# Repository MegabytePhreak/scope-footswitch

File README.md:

SCOPE-FOOTSWITCH
=================

STM32F401 based oscilloscope-footswitch interface using USBTMC.

Hardware is licensed CC-BY-SA-4.0
Software is GPLv3 for easy license compatibility with ChibiOS

Links:
* [Hackaday Coverage](https://hackaday.com/2018/12/02/keep-both-hands-on-the-probes-with-this-oscilloscope-footswitch/)
* [Initial Announcement](https://twitter.com/roukemap/status/1066811243237904384)
* [Rev.2 Batch](https://twitter.com/roukemap/status/1068734964215115776)
* [Custom Panels](https://twitter.com/roukemap/status/1072344658313908224)

Tools:

Other versions may work, this is just what is currently tested

HW:
* KiCAD 5.0.1

SW:
* arm-none-eabi-gcc (GNU Tools for ARM Embedded Processors 7-2018-q2-update) 7.3.1 20180622 (release) [ARM/embedded-7-branch revision 261907]
* GNU gdb (GNU Tools for ARM Embedded Processors 7-2018-q2-update) 8.1.0.20180315-git
* ChibiOS-RT with community USB Host framework
* libopencm3 and DFU code from BlackMagicProbe

This repo uses several submodules, make sure they are up to date.
After checking out the kicad-library repo, make sure to cd to it and run make to generate the actual KiCAD libraries.

SW Build Process:
1. Make sure the arm-none-eabi toolchain is on your path: `which arm-none-eabi-gcc`
2. Pre-build the libopencm3 library: `cd sw/ext/libopencm3 && make -j && cd ../../..`
3. Build the bootloader: `cd sw/bootloader && make -j && cd ../..`
4. Build the main application: `cd sw/scope-footswitch && make -j && cd ../..`

SW Programming process:
1. Connect SWD debugger (e.g. blackmagicprobe) to hardware
2. Connect micro-usb from pc to hardware
3. `cd sw/bootloader`
4. `./flash.sh`
5. Power cycle hardware, holding down the front panel button to force entry to the bootloader
6. `cd ../scope-footswitch`
7. `./dfu.sh`

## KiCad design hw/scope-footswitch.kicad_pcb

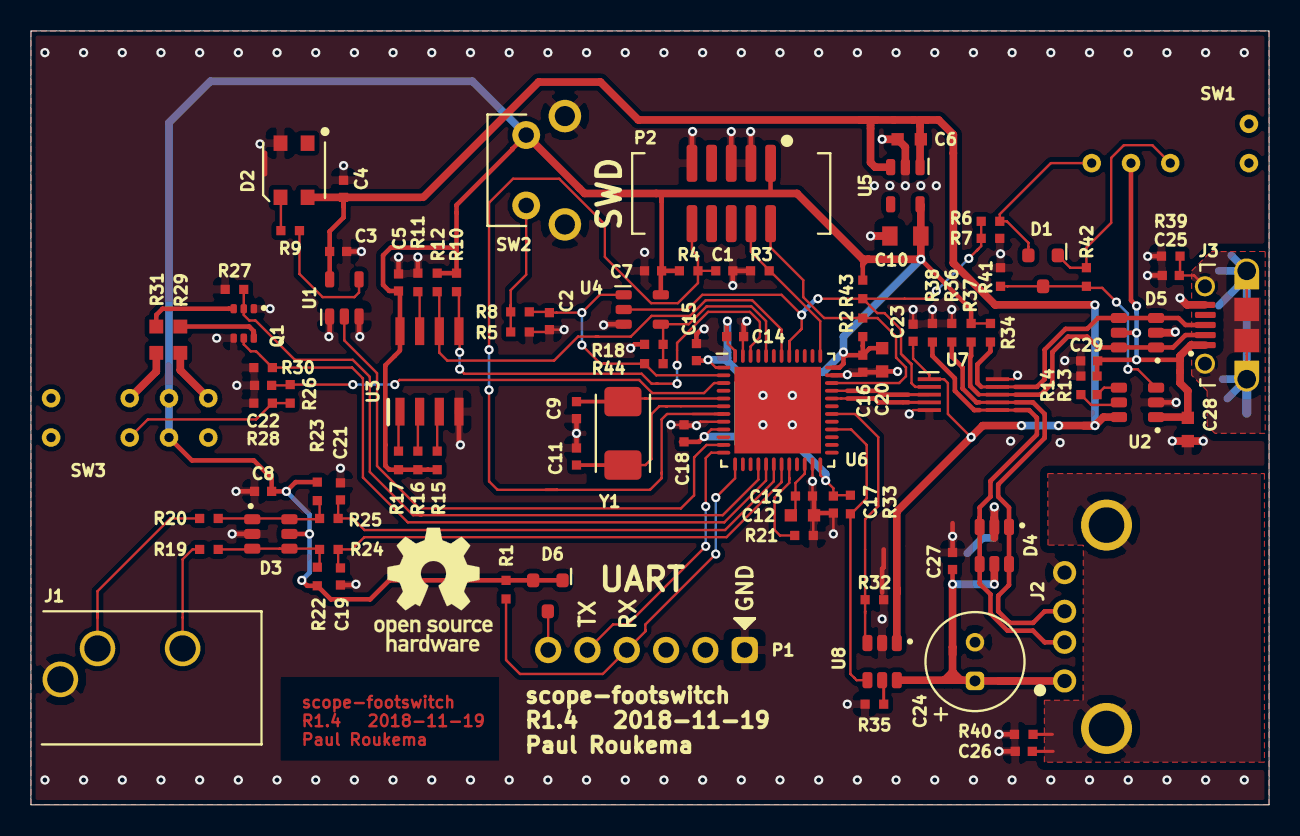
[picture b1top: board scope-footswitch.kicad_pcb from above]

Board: 2 copper layers, 80.0 x 50.0 mm, 98 parts (0 on the bottom side), 58 nets.

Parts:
C1, C2, C3, C4, C5, C7, C8, C13, C14, C15, C16, C17, C18, C19, C21, C22, C23, C27, C29: C00001; C_0402_1005M
C6, C20, C28: C00002; C_0603_1608M
C9, C11: C00033; C_0402_1005M
C10: C00004; C_0805_2012M
C12: C00007; C_0603_1608M
C24: C00003; CRADIAL_6.3x11.2_2.5
C25, C26: C00027; C_0402_1005M
D1, D6: D00006; SOT_3_950_2900X1300X1000_ONSEMI
D2: LED00006; LED_3535_NEOPIXEL_MINI
D3, D4, D5: D00003; SOT_6_950_2900X1600X1100
J1: CN00050; J_CUI_SJ1-3533NG
J2: CN00049; J_AMPHENOL_UE27AC54100
J3: CN00023; J_FCI_10118194
M1: M00028; OSHW-Logo_7.5x8mm_SilkScreen
P1: CN00052; P_FCI_68000-206
P2: CN00051; P_CNC_3221-10-0300-00
Q1: Q00002; SOT_6_650_2150X1300x1100_DIODES
R1, R4, R5, R6, R8, R11, R13, R15, R16, R17, R18, R21, R22, R23, R24, R25, R26, R27, R28, R30, R32, R33, R41: R00014; R_0402_1005M
R2, R3, R35: R00016; R_0402_1005M
R7, R36, R38: R00056; R_0402_1005M
R9: R00037; R_0402_1005M
R10, R12: R00038; R_0402_1005M
R14: R00009; R_0402_1005M
R19, R20: R00011; R_0402_1005M
R29, R31: R00080; R_0603_1608M
R34, R37: R00081; R_0402_1005M
R39, R40: R00008; R_0402_1005M
R42, R44: R00001; R_0402_1005M
R43: R00046; R_0402_1005M
SW1: M00027; SW_NKK_G13AV
SW2: M00012; SW_TL1105JA
SW3: M00026; SW_NKK_G12JVCF
U1: U00054; SOT_5_950_2900X1600X1100_DIODES
U2, U8: U00086; SOT_6_950_2800x1600x110_DIODES_SOT26
U3: U00055; SOIC_8_1270_4900X3900X1750
U4: U00087; SOT_5_950_2900X1600X1100_DIODES
U5: U00049; SOT_5_950_2900X1600X1100_DIODES
U6: U00084; QFN_48_500_7000X7000X600_ST
U7: U00085; MSOP_10_500_3000X3000X1100_ONSEMI
Y1: Y00015; XTAL_2_5000X3200X1300_ABRACON

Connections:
+3V3: C5.1, C7.1, C8.1, C10.1, C14.1, C15.1, C16.1, C17.1, C18.1, C20.2, D3.5, D6.1, D6.2, P2.1, R1.1, R2.1, R4.1, R10.2, R12.1, R15.2, R16.2, R17.2, R22.1, R23.1, R33.1, R34.1, R37.1, R43.2, SW2.1, SW3.2, SW3.5, U3.8, U4.5, U5.5, U6.1, U6.9, U6.24, U6.36, U6.48
+5V: C3.1, C4.1, C6.2, C23.1, D2.4, U1.5, U2.6, U5.1, U5.3, U7.1, U8.1
/BOOT0: R18.1, R44.1, U4.4, U6.44
/BOOT1: R21.2, U6.20
/BTN: C2.1, R8.2, R44.2, U4.1, U6.2
/BTN_R: R5.1, R8.1, SW2.2
/DEVICE_DM: D5.1, D5.6, J3.2, R37.2, U7.8
/DEVICE_DP: D5.3, D5.4, J3.3, R34.2, U7.9
/DEVICE_SHIELD: C25.1, J3.M1, J3.M2, J3.M3, J3.M4, J3.M5, J3.M6, R39.2
/EN_DEVICE: R6.1, R7.2, R43.1, U4.2, U6.41, U7.2
/EN_DEVICE_5V: D1.2, R6.2, SW1.4
/EN_HOST_5V: D1.1, R42.1, SW1.6
/FOOTSW_BTN1: C21.1, R25.2, U6.18
/FOOTSW_BTN1_R: D3.1, D3.6, R20.1, R23.2, R25.1
/FOOTSW_BTN2: C19.1, R24.2, U6.19
/FOOTSW_BTN2_R: D3.3, D3.4, R19.1, R22.2, R24.1
/HOST_DM: D4.3, D4.4, J2.2, R38.1, U7.6
/HOST_DP: D4.1, D4.6, J2.3, R36.1, U7.7
/HOST_FAULT_N: R33.2, U6.28, U8.4
/HOST_ILIM: R35.1, U8.5
/HOST_SHIELD: C26.1, J2.M1, J2.M2, R40.2
/HOST_VBUS: C24.+, C27.1, D4.5, J2.1, U8.6
/HOST_VBUS_EN: R32.1, U6.30, U8.3
/I2C_SCL: R12.2, U3.6, U6.42
/I2C_SDA: R10.1, U3.5, U6.46
/LED_DATA: D2.3, R9.1
/LED_DATA_LS: U1.2, U6.11
/LED_DATA_R: R9.2, U1.4
/MODE: C22.1, R26.2, U6.3
/MODE_LED_G: Q1.5, R30.1, U6.17
/MODE_LED_R: Q1.2, R27.1, U6.16
/MODE_R: R26.1, R28.1, SW3.3
/NRST: C1.1, P2.10, R4.2, U6.7
/PWR_EN: D1.3, R41.2, R42.2, U2.3
/STM32_DM: U6.32, U7.4
/STM32_DP: U6.33, U7.3
/SWDCLK: P2.4, R3.1, U6.37
/SWDIO: P2.2, R2.2, U6.34
/UART_RX: P1.4, R1.2, U6.13
/UART_TX: P1.5, U6.12
/VCAP: C12.2, C13.1, U6.22
/VIN_FAULT_N: R13.2, U2.4
/VIN_ILIM: R14.1, U2.5
GND: C1.2, C2.2, C3.2, C4.2, C5.2, C6.1, C7.2, C8.2, C9.1, C10.2, C11.1, C12.1, C13.2, C14.2, C15.2, C16.2, C17.2, C18.2, C19.2, C20.1, C21.2, C22.2, C23.2, C24.-, C25.2, C26.2, C27.2, C28.1, C29.2, D2.2, D3.2, D4.2, D5.2, J1.1, J2.4, J3.5, P1.1, P2.3, P2.5, P2.9, Q1.1, Q1.4, R3.2, R5.2, R7.1, R11.1, R14.2, R18.2, R21.1, R27.2, R28.2, R30.2, R32.2, R35.2, R36.2, R38.2, R39.1, R40.1, R41.1, SW2.M1, SW2.M2, U1.1, U1.3, U2.2, U3.4, U4.3, U5.2, U6.8, U6.23, U6.35, U6.47, U6.49, U7.5, U7.10, U8.2
unnamed: C9.2, U6.5, Y1.1
unnamed: C11.2, U6.6, Y1.2
unnamed: D6.3, P1.6
unnamed: J1.2, R20.2
unnamed: J1.3, R19.2
unnamed: Q1.3, R31.2
unnamed: Q1.6, R29.2
unnamed: R11.2, U3.7
unnamed: R15.1, U3.3
unnamed: R16.1, U3.2
unnamed: R17.1, U3.1
unnamed: R29.1, SW3.4
unnamed: R31.1, SW3.6
VBUS: C28.2, C29.1, D5.5, J3.1, R13.1, SW1.5, U2.1

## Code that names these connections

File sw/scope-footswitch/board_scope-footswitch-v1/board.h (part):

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 *
 * PA0  - UNUSED                    (input pullup).
 * PA1  - GPIOA_LED_DATA_LS         (alternate 2 - TIM5_CH2).
 * PA2  - UART_TX                   (alternate 7 - USART2_TX).
 * PA3  - UART_RX                   (alternate 7 - USART2_RX).
 * PA4  - UNUSED                    (input pullup).
 * PA5  - UNUSED                    (input pullup).
 * PA6  - MODE_LED_R                (alternate 3 - TIM3_CH1).
 * PA7  - MODE_LED_G                (alternate 3 - TIM3_CH2).
 * PA8  - UNUSED                    (input pullup).
 * PA9  - HOST_VBUS_EN              (output pushpull).
 * PA10 - UNUSED                    (input pullup).
 * PA11 - STM32_DM                  (alternate 10 - OTG_FS_DM).
 * PA12 - STM32_DP                  (alternate 10 - OTG_FS_DP).
 * PA13 - SWDIO                     (alternate 0 - SWDIO).
 * PA14 - SWCLK                     (alternate 0 - SWCLK).
 * PA15 - UNUSED                    (input pullup).
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/*
 * GPIOB setup:
 *
 * PB0  - FOOTSW_BTN1               (input pullup).
 * PB1  - FOOTSW_BTN2               (input pullup).
 * PB2  - BOOT1                     (input pullup).
 * PB3  - UNUSED                    (input pullup).
 * PB4  - UNUSED                    (input pullup).
 * PB5  - EN_DEVICE                 (input pullup).
 * PB6  - I2C_SCL                   (alternate 4 - I2C1_SCL).
 * PB7  - UNUSED                    (input pullup).
 * PB8  - UNUSED                    (input pullup).
 * PB9  - I2C_SDA                   (alternate 4 - I2C1_SDA).
 * PB10 - UNUSED                    (input pullup).
 * PB11 - UNUSED                    (input pullup).
 * PB12 - UNUSED                    (input pullup).
 * PB13 - UNUSED                    (input pullup).
 * PB14 - UNUSED                    (input pullup).
 * PB15 - HOST_FAULT_N              (input pullup).
 */
#define VAL_GPIOB_MODER             (PIN_MODE_INPUT(GPIOB_FOOTSW_BTN1) |    \
                                     PIN_MODE_INPUT(GPIOB_FOOTSW_BTN2) |    \
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 * PC10 - NC                        (input pullup).
 * PC11 - NC                        (input pullup).
 * PC12 - NC                        (input pullup).
 * PC13 - BTN                       (input pullup).
 * PC14 - MODE                      (input pullup).
 * PC15 - UNUSED                    (input pullup).
 */
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
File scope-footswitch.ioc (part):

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Mcu.Name=STM32F401C(B-C)Ux
Mcu.Package=UFQFPN48
Mcu.UserName=STM32F401CBUx
PA1.GPIOParameters=GPIO_Label
PA1.GPIO_Label=LED_DATA_LS
PA1.Signal=S_TIM5_CH2
PA11.GPIOParameters=GPIO_Label
PA11.GPIO_Label=STM32_DM
PA11.Mode=Device_Only
PA11.Signal=USB_OTG_FS_DM
PA12.GPIOParameters=GPIO_Label
PA12.GPIO_Label=STM32_DP
PA12.Mode=Device_Only
PA12.Signal=USB_OTG_FS_DP
PA13.GPIOParameters=GPIO_Label
PA13.GPIO_Label=SWDIO
PA13.Mode=Serial_Wire
PA13.Signal=SYS_JTMS-SWDIO
PA14.GPIOParameters=GPIO_Label
PA14.GPIO_Label=SWDCLK
PA14.Mode=Serial_Wire
PA14.Signal=SYS_JTCK-SWCLK
PA15.Signal=SYS_JTDI
PA2.GPIOParameters=GPIO_Label
PA2.GPIO_Label=UART_TX
PA2.Mode=Asynchronous
PA2.Signal=USART2_TX
PA3.GPIOParameters=GPIO_Label
PA3.GPIO_Label=UART_RX
PA3.Mode=Asynchronous
PA3.Signal=USART2_RX
PA6.GPIOParameters=GPIO_Label
PA6.GPIO_Label=MODE_LED_R
PA6.Signal=S_TIM3_CH1
PA7.GPIOParameters=GPIO_Label
PA7.GPIO_Label=MODE_LED_G
PA7.Signal=S_TIM3_CH2
PA9.GPIOParameters=GPIO_Label
PA9.GPIO_Label=HOST_VBUS_EN
PA9.Signal=GPIO_Output
PB0.GPIOParameters=GPIO_Label
PB0.GPIO_Label=FOOTSWITCH_BTN1
PB0.Signal=GPXTI0
PB1.GPIOParameters=GPIO_Label
PB1.GPIO_Label=FOOTSWITCH_BTN2
PB1.Signal=GPXTI1
PB15.GPIOParameters=GPIO_Label
PB15.GPIO_Label=HOST_FAULT_N
PB15.Signal=GPXTI15
PB2.GPIOParameters=GPIO_Label
PB2.GPIO_Label=BOOT1
PB2.Signal=GPIO_Input
PB4.Signal=SYS_JTRST
PB5.GPIOParameters=GPIO_Label
PB5.GPIO_Label=EN_DEVICE
PB5.Signal=GPXTI5
PB6.GPIOParameters=GPIO_Label
PB6.GPIO_Label=ISC_SCL
PB6.Mode=I2C
PB6.Signal=I2C1_SCL
PB9.GPIOParameters=GPIO_Label
PB9.GPIO_Label=I2C_SDA
PB9.Mode=I2C
PB9.Signal=I2C1_SDA
PC13-ANTI_TAMP.GPIOParameters=GPIO_Label
PC13-ANTI_TAMP.GPIO_Label=BTN
PC13-ANTI_TAMP.Signal=GPXTI13
PC14-OSC32_IN.GPIOParameters=GPIO_Label
PC14-OSC32_IN.GPIO_Label=MODE
PC14-OSC32_IN.Signal=GPXTI14
PH0\ -\ OSC_IN.Mode=HSE-External-Oscillator
PH0\ -\ OSC_IN.Signal=RCC_OSC_IN
PH1\ -\ OSC_OUT.Mode=HSE-External-Oscillator
PH1\ -\ OSC_OUT.Signal=RCC_OSC_OUT
RCC.HSE_VALUE=8000000
RCC.SYSCLKFreq_VALUE=72000000
RCC.SYSCLKSource=RCC_SYSCLKSOURCE_PLLCLK
board=custom

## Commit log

2018-08-06 Initial add of HW
2018-08-06 Add ChibiOS modules
2018-08-06 Add project for USB host on Nucleo board
2018-08-06 Add kicad library tables
2018-08-06 Add component documentation
2018-08-11 Initial completion of schematic and layout
2018-08-13 PCB updates and output files
2018-08-16 Layout V1.1 Fix unconnected vias, pour under crystal, USB switch pads
2018-08-25 Sync to Chibios Stable
2018-08-25 Initial TMC emulator code
2018-08-25 Move code up one level
2018-08-27 Add USB captures of target scopes
2018-08-27 Initial implementation of USBTMC device Very basic, only handles small commands
2018-08-28 Working baisc scope emulation for DPO3034 and DSO9404A:
2018-08-30 Updated kicad library version
2018-09-01 Update library
2018-09-02 Library update
2018-09-09 Switch chibios to v18.2 stable
2018-09-09 Update TMCemu to queue up to 1 in request
2018-09-09 Initial version of target board code Basic USBTMC and UI operations working
2018-09-10 Very basic footswitch functionality, Hardcoded Tektronix only for now, tested only with tmcemu.
2018-09-11 Hack in some emulation of multi-part messages as seen from tek scope
2018-09-11 Implement multi-part read support
2018-09-12 Improve dso3034 emulation
2018-09-12 Fixes for DSO3034 compatibility
2018-09-12 Improve tmc emulation, enable idn emulation based on target device
2018-09-12 Abstract scope command sets and add detection of attached device
2018-09-18 Update tmcemu from packet-oriented sizes to transfer-oriented
2018-09-18 Fix buffer sizes for transfer oriented operation, compat with DSO9404A
2018-09-19 Add clang-format confg file
2018-09-19 Clean up formatting
2018-11-13 Fix breakage with warning supression pragmas separating block from if statement
2018-11-14 Add DFU bootloader using libopencm3
2018-11-14 App updates for bootloader compatibility
2018-11-14 Add GDB init script for use with blackmagicprobe
2018-11-14 Add license headers
2018-11-14 Add README
2018-11-14 Clang-format bootloader
2018-11-14 HW Rev 13
    Tweak/DNP a bunch of parts to allow simplified power/boot control
    Update layout, including mechanical tweaks for better panel layout
2018-11-17 Remove old test project
2018-11-17 Update kicad library version
2018-11-17 Readme update
2018-11-17 Submodule updates
2018-11-17 Add readme and flash script for tmcemu
2018-11-17 Update kicad library to include readme
2018-11-17 Relocate kicad-library to github
2018-11-17 Switch to mainline ChibiOS-Contrib since USB fixes were merged
2018-11-19 Move/improve rev1.1 release structure
2018-11-19 Add notes about kicad-library setup process
2018-11-25 Rev 1.4, increase via hole size to 0.3mm
2018-11-25 Update library path to https
2018-11-26 Bootloader update: USB ID, flash size Switch to OpenMoko USB ID Correct flash size from 256K to 128K Add udev rule for user level flashing
2018-11-26 Update flash size in application linker script
2018-11-26 License updates Add top level license files Update headers on TMCEMU and templates from ChibiOS
2018-12-01 Add bootloader flashing script
2018-12-01 Update library version
2018-12-03 Fix missed license header
2018-12-03 Update README formatting
2018-12-03 Change bootloader flashing instructions to use flash.sh
2019-01-07 Initial version of HID bootloader Works with test program using hidapi-libusb on linux
2019-01-07 Initial very hacky version of HID programmer tool
2019-01-07 Integrate local HIDAPI clone for windows builds.
2019-01-09 Flesh out the bootloader programming utility
2019-01-19 Improve LED flashing and reset behaviour of bootloader
2019-01-19 Add header to flash describing version and flashing info
2019-01-19 Centralize shared files
2019-01-20 Centralize sw submodules
2019-01-26 hidprog.c enhancements for use from GUI apps
    -Enable timeouts
    -Provide mechanism to do program/verify with incremental addressing
2019-01-26 Add image header magic constants
2019-01-26 Initial version of Windows GUI update tool
2019-01-26 [common] clang-format
2019-01-29 [proggui] Add messagebox on programming error
2019-02-08 Use image header constant in application header
2019-02-08 Fix undersized string buffer
2019-02-10 [proggui] correctly handle unprogrammed targets
2019-03-19 Update support for tektronix scopes to specify exactly the data needed
2019-10-18 Add links to readme
2020-06-28 Add some gitignores
2020-06-28 Fix image header initialization constant typo
    There as a multi-character character constant in version of the constant used for marking the image header. The version of GCC used a the time appears to have ignored the extra character silently. Mo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
2020-06-28 Clean up scope handling code
2020-06-28 Quiet down USB messages
2020-06-28 Add support for Rigol scopes
    Tested on DS1104Z.
2020-06-28 Bump version
2020-06-28 Update firmware image for update gui

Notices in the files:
sw/scope-footswitch/board_scope-footswitch-v1/board.h:
Copyright (C) 2018 Paul Roukema <paul@paulroukema.com>
This program is free software: you can redistribute it and/or modify
it under the terms of the GNU General Public License as published by
the Free Software Foundation, either version 3 of the License, or
(at your option) any later version.
